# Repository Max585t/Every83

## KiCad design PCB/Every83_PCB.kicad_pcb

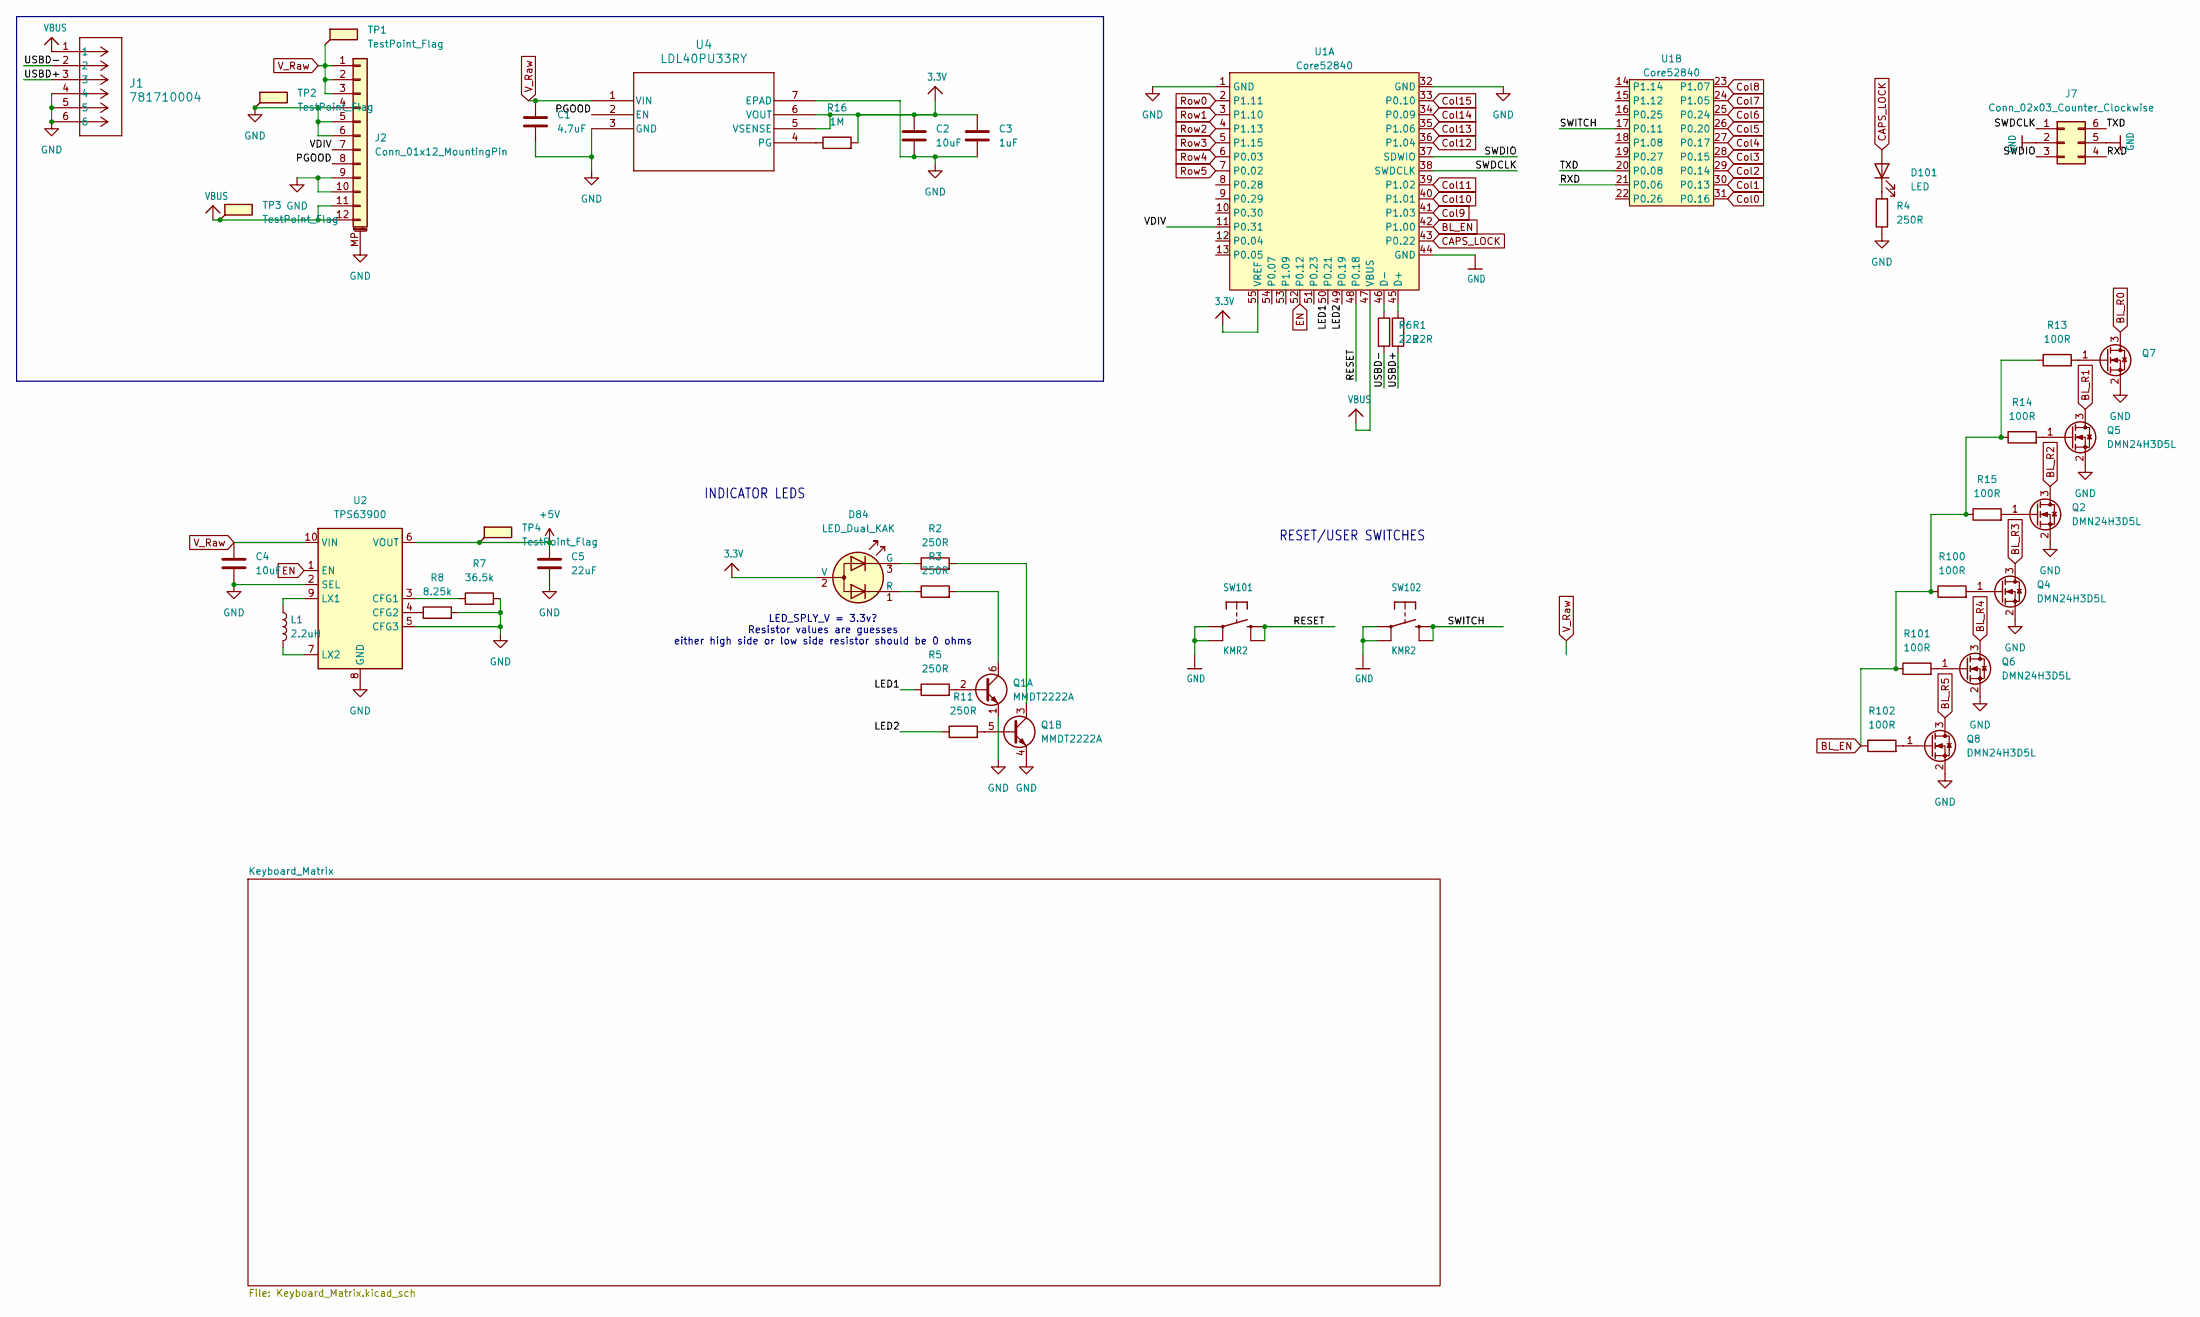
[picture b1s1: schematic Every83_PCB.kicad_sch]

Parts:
C1: 4.7uF; C_0603_1608Metric; MPN GRM188R61E475KE11D
C2: 10uF; C_0805_2012Metric; MPN GRM21BR61H106KE43L
C3: 1uF; C_0402_1005Metric; MPN GRM155R61E105KA12D
C4: 10uF; C_0603_1608Metric
C5: 22uF; C_0603_1608Metric
D84: LED_Dual_KAK; LED_Wurth_WL-SBSW
D101: LED; LED_1206_3216Metric_ReverseMount_Hole1.8x2.4mm
J1: 781710004; CON_781710004
J2: Conn_01x12_MountingPin; GCT_FFC2B28-12-G
J7: Conn_02x03_Counter_Clockwise; nRF_Programmer
L1: 2.2uH; L_0805_2012Metric
Q1: MMDT2222A; SOT-363_SC-70-6
Q2, Q4, Q5, Q6, Q7, Q8: DMN24H3D5L; SOT-23
R1, R6: 22R; R_0402_1005Metric
R2, R3, R5, R11: 250R; R_0402_1005Metric
R4: 250R; R_0603_1608Metric
R7: 36.5k; R_0402_1005Metric
R8: 8.25k; R_0402_1005Metric
R13, R14, R15, R100, R101, R102: 100R; R_0402_1005Metric
R16: 1M; R_0402_1005Metric
SW101, SW102: KMR2; BTN_KMR2_4.6X2.8
TP1, TP2, TP3, TP4: TestPoint_Flag; TestPoint_Pad_1.5x1.5mm
U1: Core52840
U2: TPS63900; WSON-10-1EP_2.5x2.5mm_P0.5mm_EP1.2x2mm_ThermalVias
U4: LDL40PU33RY; DFN6_2X2-0p65_WETTABLEFLANKS_STM-L

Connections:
3.3V: C2.1, C3.1, D84.2 (V), R16.2, U1.55 (VREF), U4.5 (VSENSE), U4.6 (VOUT)
+5V: C5.1, TP4.1, U2.6 (VOUT); also elsewhere on the board
/LED1: R5.1, U1.50 (P0.21)
/LED2: R11.1, U1.49 (P0.19)
/PGOOD: J2.8, U4.2 (EN)
/RESET: SW101.B (S), SW101.B' (S1), U1.48 (P0.18); also elsewhere on the board
/RXD: J7.4, U1.21 (P0.06); also elsewhere on the board
/SWDCLK: J7.1, U1.38 (SWDCLK); also elsewhere on the board
/SWDIO: J7.3, U1.37 (SDWIO); also elsewhere on the board
/SWITCH: SW102.B (S), SW102.B' (S1), U1.17 (P0.11); also elsewhere on the board
/TXD: J7.6, U1.20 (P0.08); also elsewhere on the board
/USBD+: J1.3, R1.2
/USBD-: J1.2, R6.2
/VDIV: J2.7, U1.11 (P0.31)
BL_EN: R13.1, R14.1, R15.1, R100.1, R101.1, R102.1, U1.42 (P1.00)
BL_R0: Q7.3 (D); also elsewhere on the board
BL_R1: Q5.3 (D); also elsewhere on the board
BL_R2: Q2.3 (D); also elsewhere on the board
BL_R3: Q4.3 (D); also elsewhere on the board
BL_R4: Q6.3 (D); also elsewhere on the board
BL_R5: Q8.3 (D); also elsewhere on the board
CAPS_LOCK: D101.2 (A), U1.43 (P0.22)
Col0: U1.31 (P0.16); also elsewhere on the board
Col1: U1.30 (P0.13); also elsewhere on the board
Col2: U1.29 (P0.14); also elsewhere on the board
Col3: U1.28 (P0.15); also elsewhere on the board
Col4: U1.27 (P0.17); also elsewhere on the board
Col5: U1.26 (P0.20); also elsewhere on the board
Col6: U1.25 (P0.24); also elsewhere on the board
Col7: U1.24 (P1.05); also elsewhere on the board
Col8: U1.23 (P1.07); also elsewhere on the board
Col9: U1.41 (P1.03); also elsewhere on the board
Col10: U1.40 (P1.01); also elsewhere on the board
Col11: U1.39 (P1.02); also elsewhere on the board
Col12: U1.36 (P1.04); also elsewhere on the board
Col13: U1.35 (P1.06); also elsewhere on the board
Col14: U1.34 (P0.09); also elsewhere on the board
Col15: U1.33 (P0.10); also elsewhere on the board
EN: U1.52 (P0.12), U2.1 (EN)
GND: C1.2, C2.2, C3.2, C4.2, C5.2, J1.4, J1.5, J1.6, J2.4, J2.5, J2.6, J2.9, J2.10, J2.MP (MountPin), J7.2, J7.5, Q1.1 (E1), Q1.4 (E2), Q2.2 (S), Q4.2 (S), Q5.2 (S), Q6.2 (S), Q7.2 (S), Q8.2 (S), R4.1, R7.2, R8.2, SW101.A, SW101.A' (P1), SW102.A, SW102.A' (P1), TP2.1, U1.1 (GND), U1.32 (GND), U1.44 (GND), U2.2 (SEL), U2.5 (CFG3), U2.8 (GND), U2.11 (GND), U4.3 (GND), U4.7 (EPAD); also elsewhere on the board
unnamed: D84.3 (G), R2.1
unnamed: D84.1 (R), R3.1
unnamed: D101.1 (K), R4.2
unnamed: Q1.2 (B1), R5.2
unnamed: Q1.6 (C1), R3.2
unnamed: Q1.5 (B2), R11.2
unnamed: Q1.3 (C2), R2.2
unnamed: Q2.1 (G), R15.2
unnamed: Q4.1 (G), R100.2
unnamed: Q5.1 (G), R14.2
unnamed: Q6.1 (G), R101.2
unnamed: Q7.1 (G), R13.2
unnamed: Q8.1 (G), R102.2
unnamed: R1.1, U1.45 (D+)
unnamed: R6.1, U1.46 (D-)
unnamed: R7.1, U2.3 (CFG1)
unnamed: R8.1, U2.4 (CFG2)
unnamed: L1.1, U2.9 (LX1)
unnamed: L1.2, U2.7 (LX2)
unnamed: R16.1, U4.4 (PG)
Row0: U1.2 (P1.11); also elsewhere on the board
Row1: U1.3 (P1.10); also elsewhere on the board
Row2: U1.4 (P1.13); also elsewhere on the board
Row3: U1.5 (P1.15); also elsewhere on the board
Row4: U1.6 (P0.03); also elsewhere on the board
Row5: U1.7 (P0.02); also elsewhere on the board
VBUS: J1.1, J2.11, J2.12, TP3.1, U1.47 (VBUS); also elsewhere on the board
V_Raw: C1.1, C4.1, J2.1, J2.2, J2.3, TP1.1, U2.10 (VIN), U4.1 (VIN); also elsewhere on the board

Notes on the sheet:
LED_SPLY_V = 3.3v? Resistor values are guesses either high side or low side resistor should be 0 ohms
INDICATOR LEDS
RESET/USER SWITCHES

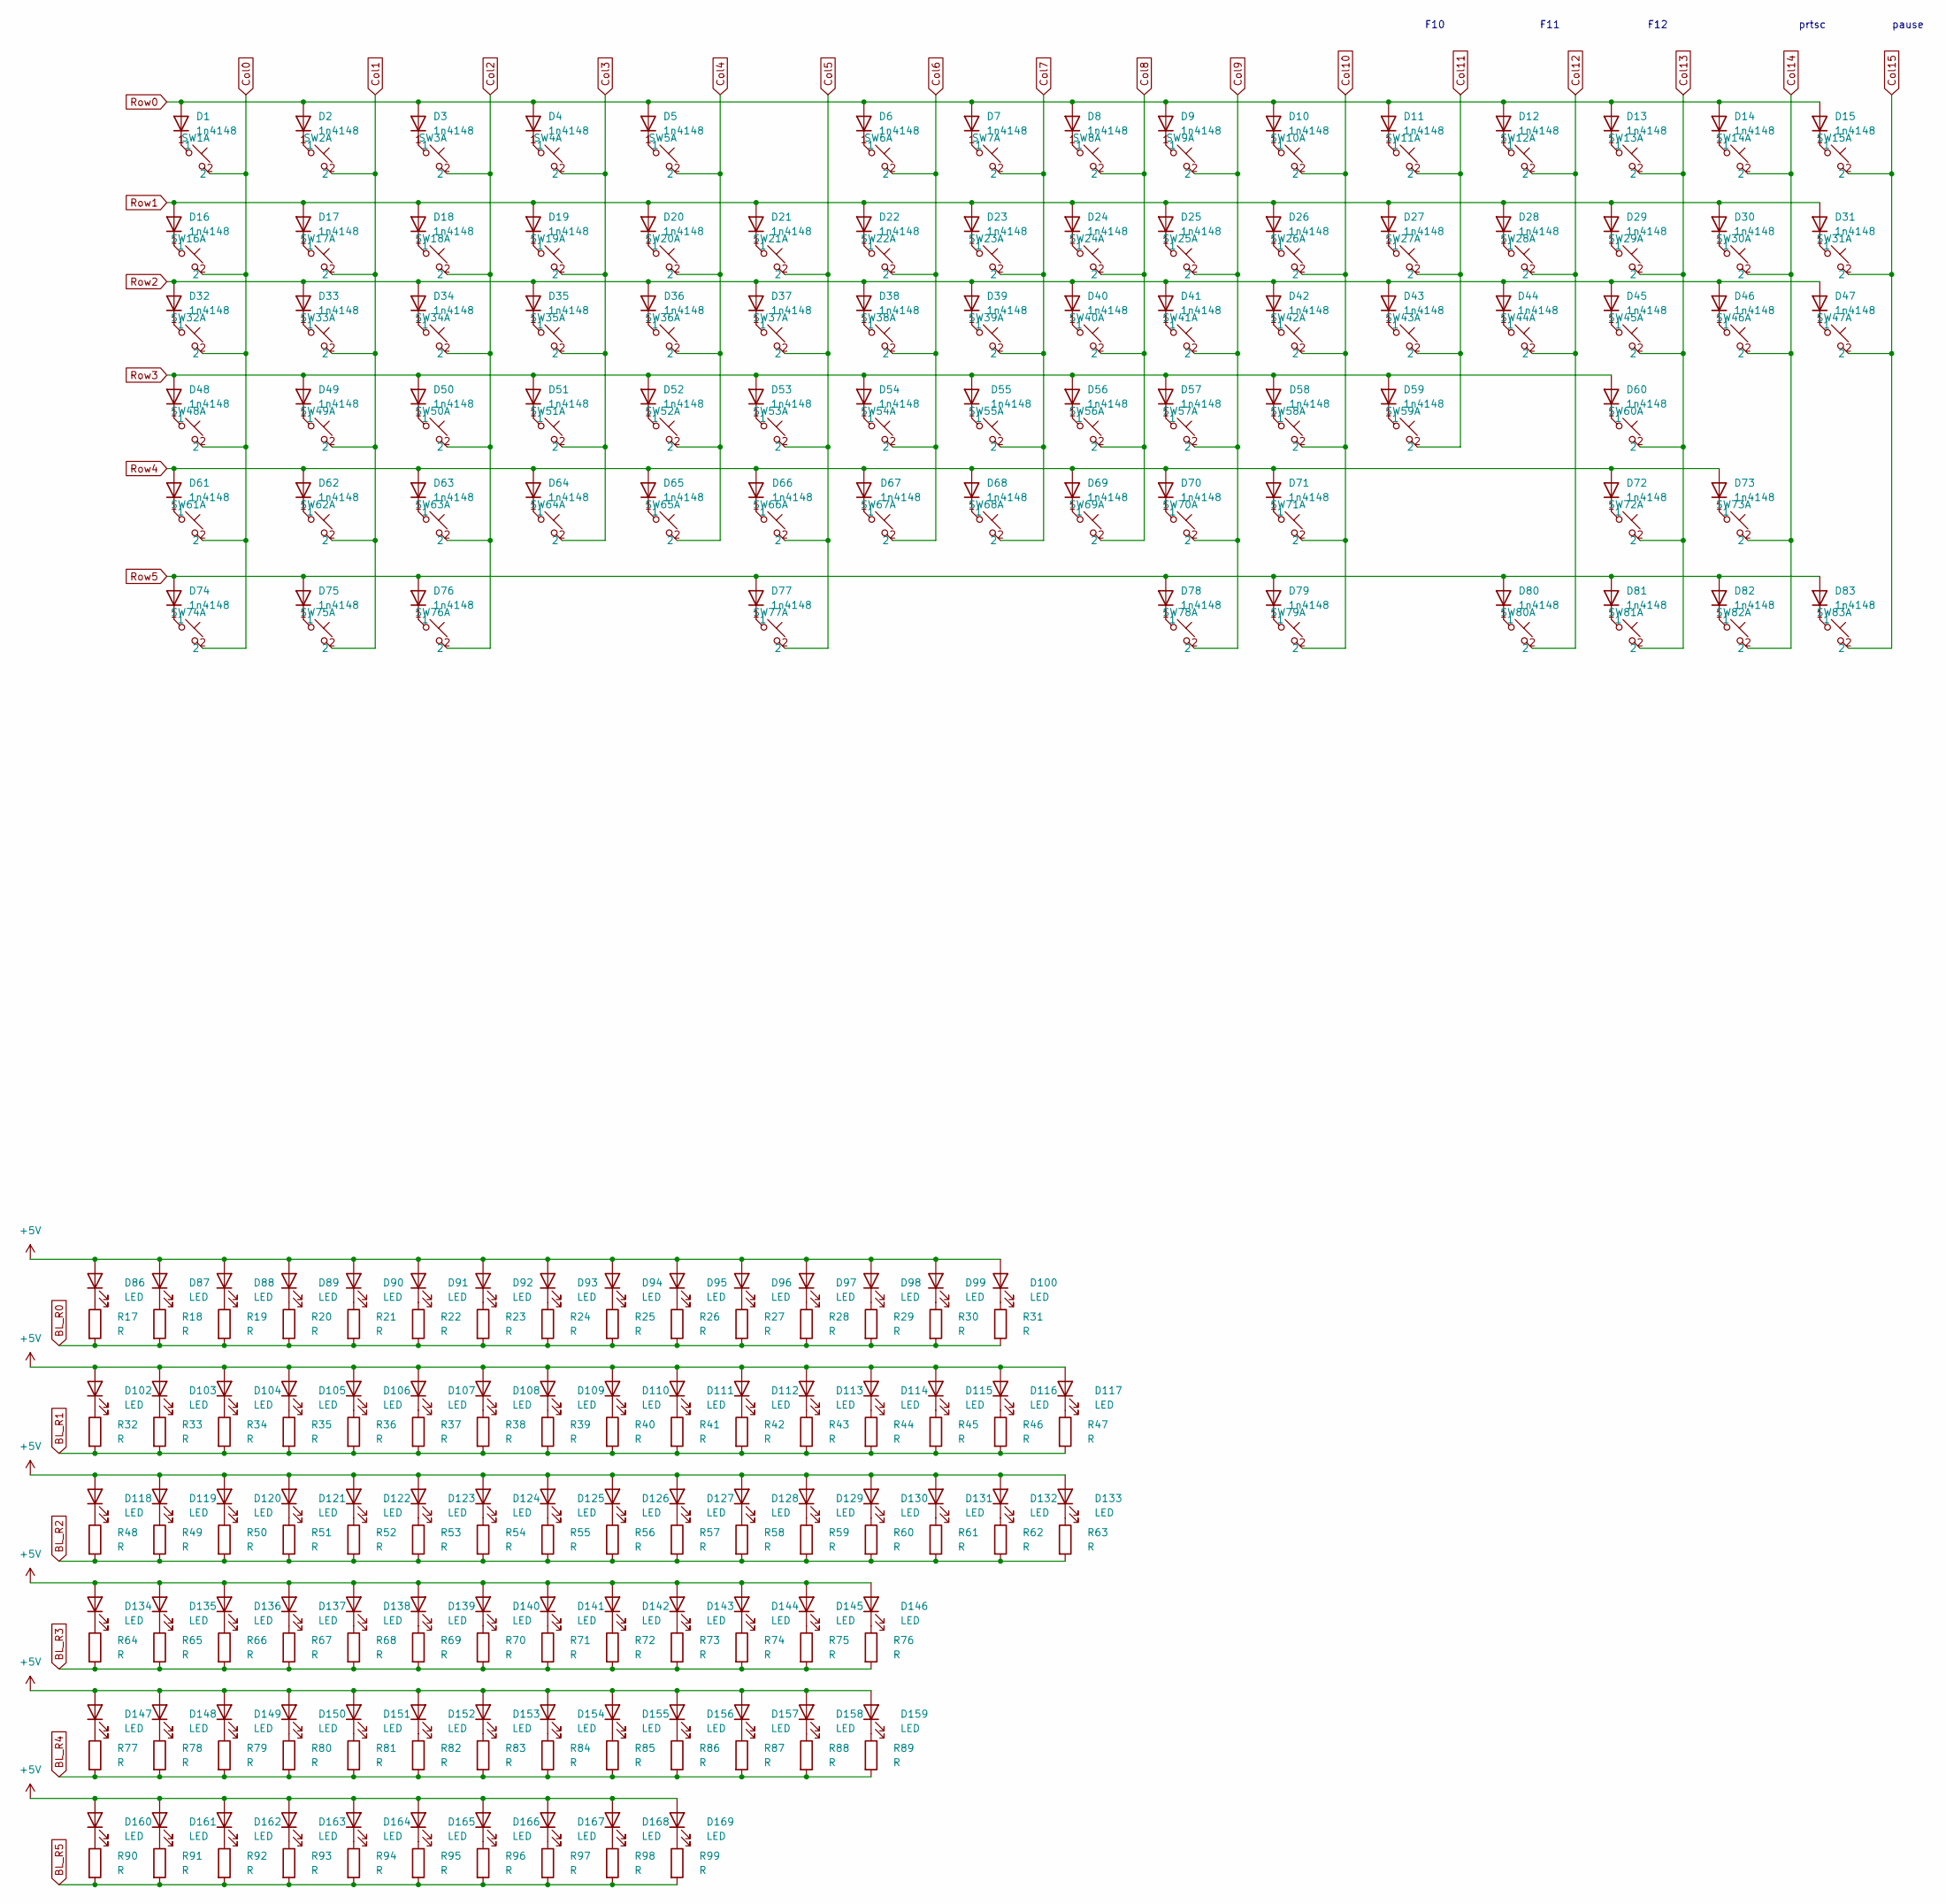
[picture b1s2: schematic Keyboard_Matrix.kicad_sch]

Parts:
D1, D2, D3, D4, D5, D6, D7, D8, D9, D10, D11, D12, D13, D14, D15, D16, D17, D18, D19, D20, D21, D22, D23, D24, D25, D26, D27, D28, D29, D30, D31, D32, D33, D34, D35, D36, D37, D38, D39, D40, D41, D42, D43, D44, D45, D46, D47, D48, D49, D50, D51, D52, D53, D54, D55, D56, D57, D58, D59, D60, D61, D62, D63, D64, D65, D66, D67, D68, D69, D70, D71, D72, D73, D74, D75, D76, D77, D78, D79, D80, D81, D82, D83: 1n4148; D_SOD-323_HandSoldering
D86, D87, D88, D89, D90, D91, D92, D93, D94, D95, D96, D97, D98, D99, D100, D102, D103, D104, D105, D106, D107, D108, D109, D110, D111, D112, D113, D114, D115, D116, D117, D118, D119, D120, D121, D122, D123, D124, D125, D126, D127, D128, D129, D130, D131, D132, D133, D134, D135, D136, D137, D138, D139, D140, D141, D142, D143, D144, D145, D146, D147, D148, D149, D150, D151, D152, D153, D154, D155, D156, D157, D158, D159, D160, D161, D162, D163, D164, D165, D166, D167, D168, D169: LED; LED_1206_3216Metric_ReverseMount_Hole1.8x2.4mm
R17, R18, R19, R20, R21, R22, R23, R24, R25, R26, R27, R28, R29, R30, R31, R32, R33, R34, R35, R36, R37, R38, R39, R40, R41, R42, R43, R44, R45, R46, R47, R48, R49, R50, R51, R52, R53, R54, R55, R56, R57, R58, R59, R60, R61, R62, R63, R64, R65, R66, R67, R68, R69, R70, R71, R72, R73, R74, R75, R76, R77, R78, R79, R80, R81, R82, R83, R84, R85, R86, R87, R88, R89, R90, R91, R92, R93, R94, R95, R96, R97, R98, R99: R; R_0603_1608Metric
SW1, SW2, SW3, SW4, SW5, SW6, SW7, SW8, SW9, SW10, SW11, SW12, SW13, SW14, SW15, SW16, SW17, SW18, SW19, SW20, SW21, SW22, SW23, SW24, SW25, SW26, SW27, SW28, SW29, SW30, SW31, SW32, SW33, SW34, SW35, SW36, SW37, SW38, SW39, SW40, SW41, SW42, SW43, SW44, SW45, SW46, SW47, SW48, SW49, SW50, SW51, SW52, SW53, SW54, SW55, SW56, SW57, SW58, SW59, SW60, SW61, SW62, SW63, SW64, SW65, SW66, SW67, SW68, SW69, SW70, SW71, SW72, SW73, SW74, SW75, SW76, SW77, SW78, SW79, SW80, SW81, SW82, SW83: gateron-ks27-choc-v1-mx-hotswap

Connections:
+5V: D86.2 (A), D87.2 (A), D88.2 (A), D89.2 (A), D90.2 (A), D91.2 (A), D92.2 (A), D93.2 (A), D94.2 (A), D95.2 (A), D96.2 (A), D97.2 (A), D98.2 (A), D99.2 (A), D100.2 (A), D102.2 (A), D103.2 (A), D104.2 (A), D105.2 (A), D106.2 (A), D107.2 (A), D108.2 (A), D109.2 (A), D110.2 (A), D111.2 (A), D112.2 (A), D113.2 (A), D114.2 (A), D115.2 (A), D116.2 (A), D117.2 (A), D118.2 (A), D119.2 (A), D120.2 (A), D121.2 (A), D122.2 (A), D123.2 (A), D124.2 (A), D125.2 (A), D126.2 (A), D127.2 (A), D128.2 (A), D129.2 (A), D130.2 (A), D131.2 (A), D132.2 (A), D133.2 (A), D134.2 (A), D135.2 (A), D136.2 (A), D137.2 (A), D138.2 (A), D139.2 (A), D140.2 (A), D141.2 (A), D142.2 (A), D143.2 (A), D144.2 (A), D145.2 (A), D146.2 (A), D147.2 (A), D148.2 (A), D149.2 (A), D150.2 (A), D151.2 (A), D152.2 (A), D153.2 (A), D154.2 (A), D155.2 (A), D156.2 (A), D157.2 (A), D158.2 (A), D159.2 (A), D160.2 (A), D161.2 (A), D162.2 (A), D163.2 (A), D164.2 (A), D165.2 (A), D166.2 (A), D167.2 (A), D168.2 (A), D169.2 (A); also elsewhere on the board
BL_R0: R17.2, R18.2, R19.2, R20.2, R21.2, R22.2, R23.2, R24.2, R25.2, R26.2, R27.2, R28.2, R29.2, R30.2, R31.2; also elsewhere on the board
BL_R1: R32.2, R33.2, R34.2, R35.2, R36.2, R37.2, R38.2, R39.2, R40.2, R41.2, R42.2, R43.2, R44.2, R45.2, R46.2, R47.2; also elsewhere on the board
BL_R2: R48.2, R49.2, R50.2, R51.2, R52.2, R53.2, R54.2, R55.2, R56.2, R57.2, R58.2, R59.2, R60.2, R61.2, R62.2, R63.2; also elsewhere on the board
BL_R3: R64.2, R65.2, R66.2, R67.2, R68.2, R69.2, R70.2, R71.2, R72.2, R73.2, R74.2, R75.2, R76.2; also elsewhere on the board
BL_R4: R77.2, R78.2, R79.2, R80.2, R81.2, R82.2, R83.2, R84.2, R85.2, R86.2, R87.2, R88.2, R89.2; also elsewhere on the board
BL_R5: R90.2, R91.2, R92.2, R93.2, R94.2, R95.2, R96.2, R97.2, R98.2, R99.2; also elsewhere on the board
Col0: SW1.2, SW16.2, SW32.2, SW48.2, SW61.2, SW74.2; also elsewhere on the board
Col1: SW2.2, SW17.2, SW33.2, SW49.2, SW62.2, SW75.2; also elsewhere on the board
Col2: SW3.2, SW18.2, SW34.2, SW50.2, SW63.2, SW76.2; also elsewhere on the board
Col3: SW4.2, SW19.2, SW35.2, SW51.2, SW64.2; also elsewhere on the board
Col4: SW5.2, SW20.2, SW36.2, SW52.2, SW65.2; also elsewhere on the board
Col5: SW21.2, SW37.2, SW53.2, SW66.2, SW77.2; also elsewhere on the board
Col6: SW6.2, SW22.2, SW38.2, SW54.2, SW67.2; also elsewhere on the board
Col7: SW7.2, SW23.2, SW39.2, SW55.2, SW68.2; also elsewhere on the board
Col8: SW8.2, SW24.2, SW40.2, SW56.2, SW69.2; also elsewhere on the board
Col9: SW9.2, SW25.2, SW41.2, SW57.2, SW70.2, SW78.2; also elsewhere on the board
Col10: SW10.2, SW26.2, SW42.2, SW58.2, SW71.2, SW79.2; also elsewhere on the board
Col11: SW11.2, SW27.2, SW43.2, SW59.2; also elsewhere on the board
Col12: SW12.2, SW28.2, SW44.2, SW80.2; also elsewhere on the board
Col13: SW13.2, SW29.2, SW45.2, SW60.2, SW72.2, SW81.2; also elsewhere on the board
Col14: SW14.2, SW30.2, SW46.2, SW73.2, SW82.2; also elsewhere on the board
Col15: SW15.2, SW31.2, SW47.2, SW83.2; also elsewhere on the board
unnamed: D1.1 (K), SW1.1
unnamed: D2.1 (K), SW2.1
unnamed: D3.1 (K), SW3.1
unnamed: D4.1 (K), SW4.1
unnamed: D5.1 (K), SW5.1
unnamed: D6.1 (K), SW6.1
unnamed: D7.1 (K), SW7.1
unnamed: D8.1 (K), SW8.1
unnamed: D9.1 (K), SW9.1
unnamed: D10.1 (K), SW10.1
unnamed: D11.1 (K), SW11.1
unnamed: D12.1 (K), SW12.1
unnamed: D13.1 (K), SW13.1
unnamed: D14.1 (K), SW14.1
unnamed: D15.1 (K), SW15.1
unnamed: D16.1 (K), SW16.1
unnamed: D17.1 (K), SW17.1
unnamed: D18.1 (K), SW18.1
unnamed: D19.1 (K), SW19.1
unnamed: D20.1 (K), SW20.1
unnamed: D21.1 (K), SW21.1
unnamed: D22.1 (K), SW22.1
unnamed: D23.1 (K), SW23.1
unnamed: D24.1 (K), SW24.1
unnamed: D25.1 (K), SW25.1
unnamed: D26.1 (K), SW26.1
unnamed: D27.1 (K), SW27.1
unnamed: D28.1 (K), SW28.1
unnamed: D29.1 (K), SW29.1
unnamed: D30.1 (K), SW30.1
unnamed: D31.1 (K), SW31.1
unnamed: D32.1 (K), SW32.1
unnamed: D33.1 (K), SW33.1
unnamed: D34.1 (K), SW34.1
unnamed: D35.1 (K), SW35.1
unnamed: D36.1 (K), SW36.1
unnamed: D37.1 (K), SW37.1
unnamed: D38.1 (K), SW38.1
unnamed: D39.1 (K), SW39.1
unnamed: D40.1 (K), SW40.1
unnamed: D41.1 (K), SW41.1
unnamed: D42.1 (K), SW42.1
unnamed: D43.1 (K), SW43.1
unnamed: D44.1 (K), SW44.1
unnamed: D45.1 (K), SW45.1
unnamed: D46.1 (K), SW46.1
unnamed: D47.1 (K), SW47.1
unnamed: D48.1 (K), SW48.1
unnamed: D49.1 (K), SW49.1
unnamed: D50.1 (K), SW50.1
unnamed: D51.1 (K), SW51.1
unnamed: D52.1 (K), SW52.1
unnamed: D53.1 (K), SW53.1
unnamed: D54.1 (K), SW54.1
unnamed: D55.1 (K), SW55.1
unnamed: D56.1 (K), SW56.1
unnamed: D57.1 (K), SW57.1
unnamed: D58.1 (K), SW58.1
unnamed: D59.1 (K), SW59.1
unnamed: D60.1 (K), SW60.1
unnamed: D61.1 (K), SW61.1
unnamed: D62.1 (K), SW62.1
unnamed: D63.1 (K), SW63.1
unnamed: D64.1 (K), SW64.1
unnamed: D65.1 (K), SW65.1
unnamed: D66.1 (K), SW66.1
unnamed: D67.1 (K), SW67.1
unnamed: D68.1 (K), SW68.1
unnamed: D69.1 (K), SW69.1
unnamed: D70.1 (K), SW70.1
unnamed: D71.1 (K), SW71.1
unnamed: D72.1 (K), SW72.1
unnamed: D73.1 (K), SW73.1
unnamed: D74.1 (K), SW74.1
unnamed: D75.1 (K), SW75.1
unnamed: D76.1 (K), SW76.1
unnamed: D77.1 (K), SW77.1
unnamed: D78.1 (K), SW78.1
unnamed: D79.1 (K), SW79.1
unnamed: D80.1 (K), SW80.1
unnamed: D81.1 (K), SW81.1
unnamed: D82.1 (K), SW82.1
unnamed: D83.1 (K), SW83.1
unnamed: D86.1 (K), R17.1
unnamed: D87.1 (K), R18.1
unnamed: D88.1 (K), R19.1
unnamed: D89.1 (K), R20.1
unnamed: D90.1 (K), R21.1
unnamed: D91.1 (K), R22.1
unnamed: D92.1 (K), R23.1
unnamed: D93.1 (K), R24.1
unnamed: D94.1 (K), R25.1
unnamed: D95.1 (K), R26.1
unnamed: D96.1 (K), R27.1
unnamed: D97.1 (K), R28.1
unnamed: D98.1 (K), R29.1
unnamed: D99.1 (K), R30.1
unnamed: D100.1 (K), R31.1
unnamed: D102.1 (K), R32.1
unnamed: D103.1 (K), R33.1
unnamed: D104.1 (K), R34.1
unnamed: D105.1 (K), R35.1
unnamed: D106.1 (K), R36.1
unnamed: D107.1 (K), R37.1
unnamed: D108.1 (K), R38.1
unnamed: D109.1 (K), R39.1
unnamed: D110.1 (K), R40.1
unnamed: D111.1 (K), R41.1
unnamed: D112.1 (K), R42.1
unnamed: D113.1 (K), R43.1
unnamed: D114.1 (K), R44.1
unnamed: D115.1 (K), R45.1
unnamed: D116.1 (K), R46.1
unnamed: D117.1 (K), R47.1
unnamed: D118.1 (K), R48.1
unnamed: D119.1 (K), R49.1
unnamed: D120.1 (K), R50.1
unnamed: D121.1 (K), R51.1
unnamed: D122.1 (K), R52.1
unnamed: D123.1 (K), R53.1
unnamed: D124.1 (K), R54.1
unnamed: D125.1 (K), R55.1
unnamed: D126.1 (K), R56.1
unnamed: D127.1 (K), R57.1
unnamed: D128.1 (K), R58.1
unnamed: D129.1 (K), R59.1
unnamed: D130.1 (K), R60.1
unnamed: D131.1 (K), R61.1
unnamed: D132.1 (K), R62.1
unnamed: D133.1 (K), R63.1
unnamed: D134.1 (K), R64.1
unnamed: D135.1 (K), R65.1
unnamed: D136.1 (K), R66.1
unnamed: D137.1 (K), R67.1
unnamed: D138.1 (K), R68.1
unnamed: D139.1 (K), R69.1
unnamed: D140.1 (K), R70.1
unnamed: D141.1 (K), R71.1
unnamed: D142.1 (K), R72.1
unnamed: D143.1 (K), R73.1
unnamed: D144.1 (K), R74.1
unnamed: D145.1 (K), R75.1
unnamed: D146.1 (K), R76.1
unnamed: D147.1 (K), R77.1
unnamed: D148.1 (K), R78.1
unnamed: D149.1 (K), R79.1
unnamed: D150.1 (K), R80.1
unnamed: D151.1 (K), R81.1
unnamed: D152.1 (K), R82.1
unnamed: D153.1 (K), R83.1
unnamed: D154.1 (K), R84.1
unnamed: D155.1 (K), R85.1
unnamed: D156.1 (K), R86.1
unnamed: D157.1 (K), R87.1
unnamed: D158.1 (K), R88.1
unnamed: D159.1 (K), R89.1
unnamed: D160.1 (K), R90.1
unnamed: D161.1 (K), R91.1
unnamed: D162.1 (K), R92.1
unnamed: D163.1 (K), R93.1
unnamed: D164.1 (K), R94.1
unnamed: D165.1 (K), R95.1
unnamed: D166.1 (K), R96.1
unnamed: D167.1 (K), R97.1
unnamed: D168.1 (K), R98.1
unnamed: D169.1 (K), R99.1
Row0: D1.2 (A), D2.2 (A), D3.2 (A), D4.2 (A), D5.2 (A), D6.2 (A), D7.2 (A), D8.2 (A), D9.2 (A), D10.2 (A), D11.2 (A), D12.2 (A), D13.2 (A), D14.2 (A), D15.2 (A); also elsewhere on the board
Row1: D16.2 (A), D17.2 (A), D18.2 (A), D19.2 (A), D20.2 (A), D21.2 (A), D22.2 (A), D23.2 (A), D24.2 (A), D25.2 (A), D26.2 (A), D27.2 (A), D28.2 (A), D29.2 (A), D30.2 (A), D31.2 (A); also elsewhere on the board
Row2: D32.2 (A), D33.2 (A), D34.2 (A), D35.2 (A), D36.2 (A), D37.2 (A), D38.2 (A), D39.2 (A), D40.2 (A), D41.2 (A), D42.2 (A), D43.2 (A), D44.2 (A), D45.2 (A), D46.2 (A), D47.2 (A); also elsewhere on the board
Row3: D48.2 (A), D49.2 (A), D50.2 (A), D51.2 (A), D52.2 (A), D53.2 (A), D54.2 (A), D55.2 (A), D56.2 (A), D57.2 (A), D58.2 (A), D59.2 (A), D60.2 (A); also elsewhere on the board
Row4: D61.2 (A), D62.2 (A), D63.2 (A), D64.2 (A), D65.2 (A), D66.2 (A), D67.2 (A), D68.2 (A), D69.2 (A), D70.2 (A), D71.2 (A), D72.2 (A), D73.2 (A); also elsewhere on the board
Row5: D74.2 (A), D75.2 (A), D76.2 (A), D77.2 (A), D78.2 (A), D79.2 (A), D80.2 (A), D81.2 (A), D82.2 (A), D83.2 (A); also elsewhere on the board

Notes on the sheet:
F10
prtsc
F12
pause
F11

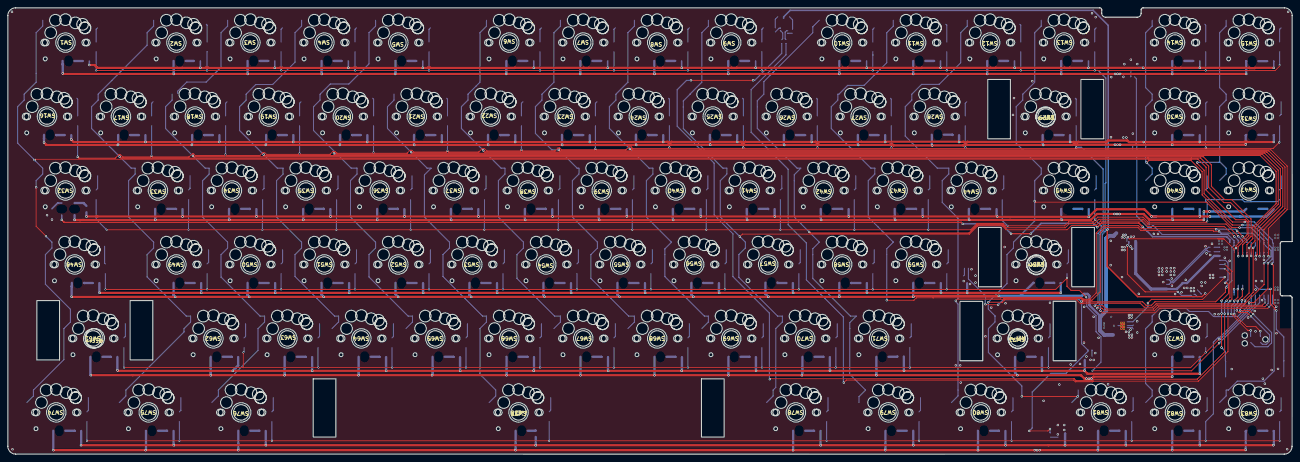
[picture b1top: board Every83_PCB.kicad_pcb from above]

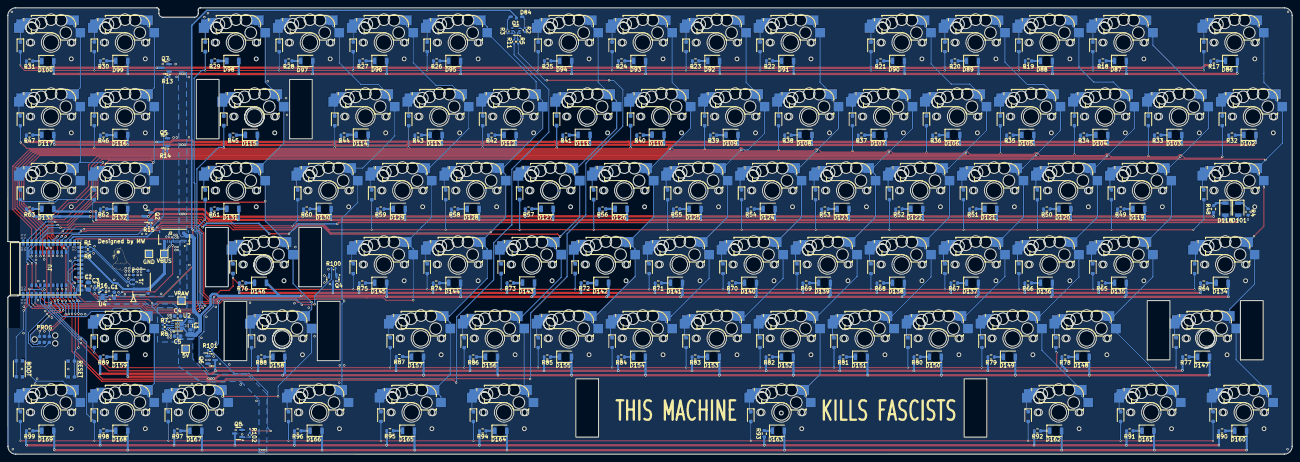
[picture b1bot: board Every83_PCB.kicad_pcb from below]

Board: 2 copper layers, 330.8 x 114.9 mm, 375 parts (291 on the bottom side), 234 nets.

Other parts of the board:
5V: TestPoint_Flag; TestPoint_Pad_1.5x1.5mm
BOOT: KMR2; BTN_KMR2_4.6X2.8
GND: TestPoint_Flag; TestPoint_Pad_1.5x1.5mm
PROG: Conn_02x03_Counter_Clockwise; nRF_Programmer
RESET: KMR2; BTN_KMR2_4.6X2.8
VBUS: TestPoint_Flag; TestPoint_Pad_1.5x1.5mm
VRAW: TestPoint_Flag; TestPoint_Pad_1.5x1.5mm

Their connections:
+5V: 5V.1; also elsewhere on the board
/RESET: RESET.B (S), RESET.B' (S1); also elsewhere on the board
/RXD: PROG.4; also elsewhere on the board
/SWDCLK: PROG.1; also elsewhere on the board
/SWDIO: PROG.3; also elsewhere on the board
/SWITCH: BOOT.B (S), BOOT.B' (S1); also elsewhere on the board
/TXD: PROG.6; also elsewhere on the board
GND: BOOT.A, BOOT.A' (P1), GND.1, PROG.2, PROG.5, RESET.A, RESET.A' (P1); also elsewhere on the board
VBUS: VBUS.1; also elsewhere on the board
V_Raw: VRAW.1; also elsewhere on the board

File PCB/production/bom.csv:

Designator,Footprint,Quantity,Value,LCSC Part #
"5V, GND, VBUS, VRAW",TestPoint_Pad_1.5x1.5mm,4,TestPoint_Flag,
"BOOT, RESET",BTN_KMR2_4.6X2.8,2,KMR2,
C1,0603,1,4.7uF,GRM188R61E475KE11D
C2,0805,1,10uF,GRM21BR61H106KE43L
C3,0402,1,1uF,GRM155R61E105KA12D
C4,0603,1,10uF,
C5,0603,1,22uF,
"D1, D10, D11, D12, D13, D14, D15, D16, D17, D18, D19, D2, D20, D21, D22, D23, D24, D25, D26, D27, D28, D29, D3, D30, D31, D32, D33, D34, D35, D36, D37, D38, D39, D4, D40, D41, D42, D43, D44, D45, D46, D47, D48, D49, D5, D50, D51, D52, D53, D54, D55, D56, D57, D58, D59, D6, D60, D61, D62, D63, D64, D65, D66, D67, D68, D69, D7, D70, D71, D72, D73, D74, D75, D76, D77, D78, D79, D8, D80, D81, D82, D83, D9",D_SOD-323_HandSoldering,83,1n4148,
"D100, D101, D102, D103, D104, D105, D106, D107, D108, D109, D110, D111, D112, D113, D114, D115, D116, D117, D118, D119, D120, D121, D122, D123, D124, D125, D126, D127, D128, D129, D130, D131, D132, D133, D134, D135, D136, D137, D138, D139, D140, D141, D142, D143, D144, D145, D146, D147, D148, D149, D150, D151, D152, D153, D154, D155, D156, D157, D158, D159, D160, D161, D162, D163, D164, D165, D166, D167, D168, D169, D86, D87, D88, D89, D90, D91, D92, D93, D94, D95, D96, D97, D98, D99",1206,84,LED,
D84,LED_Wurth_WL-SBSW,1,LED_Dual_KAK,
J1,CON_781710004,1,781710004,
J2,GCT_FFC2B28-12-G,1,Conn_01x12_MountingPin,
L1,0805,1,2.2uH,
PROG,nRF_Programmer,1,Conn_02x03_Counter_Clockwise,
Q1,SOT-363_SC-70-6,1,MMDT2222A,
"Q2, Q4, Q5, Q6, Q7, Q8",SOT-23,6,DMN24H3D5L,
"R1, R6",0402,2,22R,
"R100, R101, R102, R13, R14, R15",0402,6,100R,
"R11, R2, R3, R5",0402,4,250R,
R16,0402,1,1M,
"R17, R18, R19, R20, R21, R22, R23, R24, R25, R26, R27, R28, R29, R30, R31, R32, R33, R34, R35, R36, R37, R38, R39, R40, R41, R42, R43, R44, R45, R46, R47, R48, R49, R50, R51, R52, R53, R54, R55, R56, R57, R58, R59, R60, R61, R62, R63, R64, R65, R66, R67, R68, R69, R70, R71, R72, R73, R74, R75, R76, R77, R78, R79, R80, R81, R82, R83, R84, R85, R86, R87, R88, R89, R90, R91, R92, R93, R94, R95, R96, R97, R98, R99",0603,83,R,
R4,0603,1,250R,
R7,0402,1,36.5k,
R8,0402,1,8.25k,
"SW1, SW10, SW11, SW12, SW13, SW14, SW15, SW16, SW17, SW18, SW19, SW2, SW20, SW21, SW22, SW23, SW24, SW25, SW26, SW27, SW28, SW29, SW3, SW30, SW31, SW32, SW33, SW34, SW35, SW36, SW37, SW38, SW39, SW4, SW40, SW41, SW42, SW43, SW44, SW45, SW46, SW47, SW48, SW49, SW5, SW50, SW51, SW52, SW53, SW54, SW55, SW56, SW57, SW58, SW59, SW6, SW60, SW61, SW62, SW63, SW64, SW65, SW66, SW67, SW68, SW69, SW7, SW70, SW71, SW72, SW73, SW74, SW75, SW76, SW77, SW78, SW79, SW8, SW80, SW81, SW82, SW83, SW9",gateron-ks27-choc-v1-mx-hotswap,83,~,
U1,Core52840,1,Core52840,
U2,WSON-10-1EP_2.5x2.5mm_P0.5mm_EP1.2x2mm_ThermalVias,1,TPS63900,
U4,DFN6_2X2-0p65_WETTABLEFLANKS_STM-L,1,LDL40PU33RY,

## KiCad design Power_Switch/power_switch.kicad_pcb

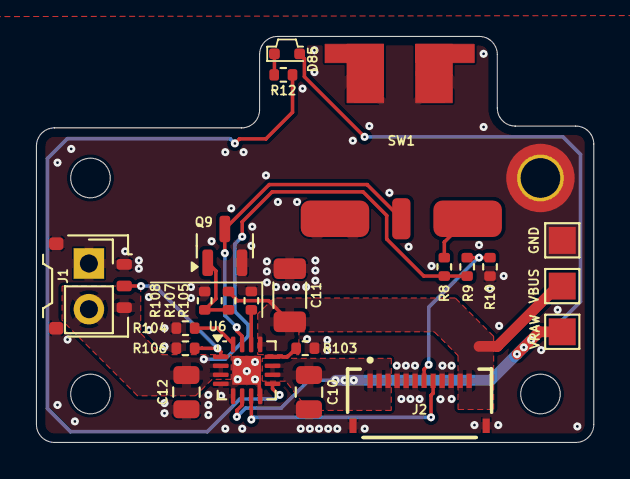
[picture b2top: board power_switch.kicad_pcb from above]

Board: 2 copper layers, 31.0 x 22.6 mm, 27 parts (0 on the bottom side), 15 nets.

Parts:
C10, C12: 4.7uF; C_0805_2012Metric
C11: 1uF; C_1206_3216Metric
D85: LED; LED_WURTH_155060AS75300
GND: TestPoint_Flag; TestPoint_Pad_1.5x1.5mm
H1, H3, H4: MountingHole; MountingHole_2.2mm_M2_ISO14580
H2: MountingHole; MountingHole_2.2mm_M2_ISO14580_Pad_TopBottom
J1: Conn_01x03_Pin; Molex_Pico-EZmate_78171-0003_1x03-1MP_P1.20mm_Vertical
J2: GCT_FFC2B28-12-G
J6: Conn_01x02_Pin; PinSocket_1x02_P2.54mm_Vertical
Q9: 2N7002; SOT-23
R8, R9, R10: 100k; R_0402_1005Metric
R12: 1.5k; R_0402_1005Metric
R103: 1.87k; R_0402_1005Metric
R104: 1k; R_0402_1005Metric
R105: 47k; R_0402_1005Metric
R106, R108: 10k; R_0402_1005Metric
R107: 100R; R_0402_1005Metric
SW1: SW_SPDT; ET01M3D1SAPE
U6: BQ24075RGT; VQFN-16-1EP_3x3mm_P0.5mm_EP1.6x1.6mm
VBUS: TestPoint_Flag; TestPoint_Pad_1.5x1.5mm
VRAW: TestPoint_Flag; TestPoint_Pad_1.5x1.5mm

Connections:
/PGOOD: J2.8, U6.7 (~PGOOD)
/TS: J1.2, R106.1, U6.1 (TS)
/VDIV: J2.7, R9.2, R10.1
GND: C10.2, C11.2, C12.2, GND.1, H2.1, J1.1, J1.MP, J2.4, J2.5, J2.6, J2.9, J2.10, J2.S1 (SHIELD), J2.S2 (SHIELD__1), J6.1, Q9.2 (S), R10.2, R103.2, R104.2, R105.2, R106.2, R108.2, SW1.1 (A), SW1.MP, U6.4 (~CE), U6.5 (EN2), U6.8 (VSS), U6.17 (VSS)
unnamed: D85.1 (K), R12.1
unnamed: Q9.1 (G), R107.1, R108.1
unnamed: R8.2, SW1.3 (C)
unnamed: R103.1, U6.12 (ILIM)
unnamed: R104.1, U6.16 (ISET)
unnamed: R105.1, U6.14 (TMR)
unnamed: R12.2, U6.9 (~CHG)
SYSOFF: Q9.3 (D), SW1.2 (B), U6.15 (SYSOFF)
VBAT: C12.1, J1.3, J6.2, R8.1, R9.1, U6.2 (BAT), U6.3 (BAT)
VBUS: C11.1, J2.11, J2.12, R107.2, U6.13 (IN), VBUS.1
V_Raw: C10.1, D85.2 (A), J2.1, J2.2, J2.3, U6.6 (EN1), U6.10 (OUT), U6.11 (OUT), VRAW.1

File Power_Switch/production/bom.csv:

Designator,Footprint,Quantity,Value,LCSC Part #
"C10, C12",0805,2,4.7uF,
C11,1206,1,1uF,
D85,LED_WURTH_155060AS75300,1,LED,
"GND, VBUS, VRAW",TestPoint_Pad_1.5x1.5mm,3,TestPoint_Flag,
J1,Molex_Pico-EZmate_78171-0003_1x03-1MP_P1.20mm_Vertical,1,Conn_01x03_Pin,
J2,GCT_FFC2B28-12-G,1,GCT_FFC2B28-12-G,
J6,PinSocket_1x02_P2.54mm_Vertical,1,Conn_01x02_Pin,
Q9,SOT-23,1,2N7002,
"R10, R8, R9",0402,3,100k,
R103,0402,1,1.87k,RT0402BRD071K87L
R104,0402,1,1k,
R105,0402,1,47k,
"R106, R108",0402,2,10k,
R107,0402,1,100R,
R12,0402,1,1.5k,
SW1,ET01M3D1SAPE,1,SW_SPDT,
U6,VQFN-16-1EP_3x3mm_P0.5mm_EP1.6x1.6mm,1,BQ24075RGT,
